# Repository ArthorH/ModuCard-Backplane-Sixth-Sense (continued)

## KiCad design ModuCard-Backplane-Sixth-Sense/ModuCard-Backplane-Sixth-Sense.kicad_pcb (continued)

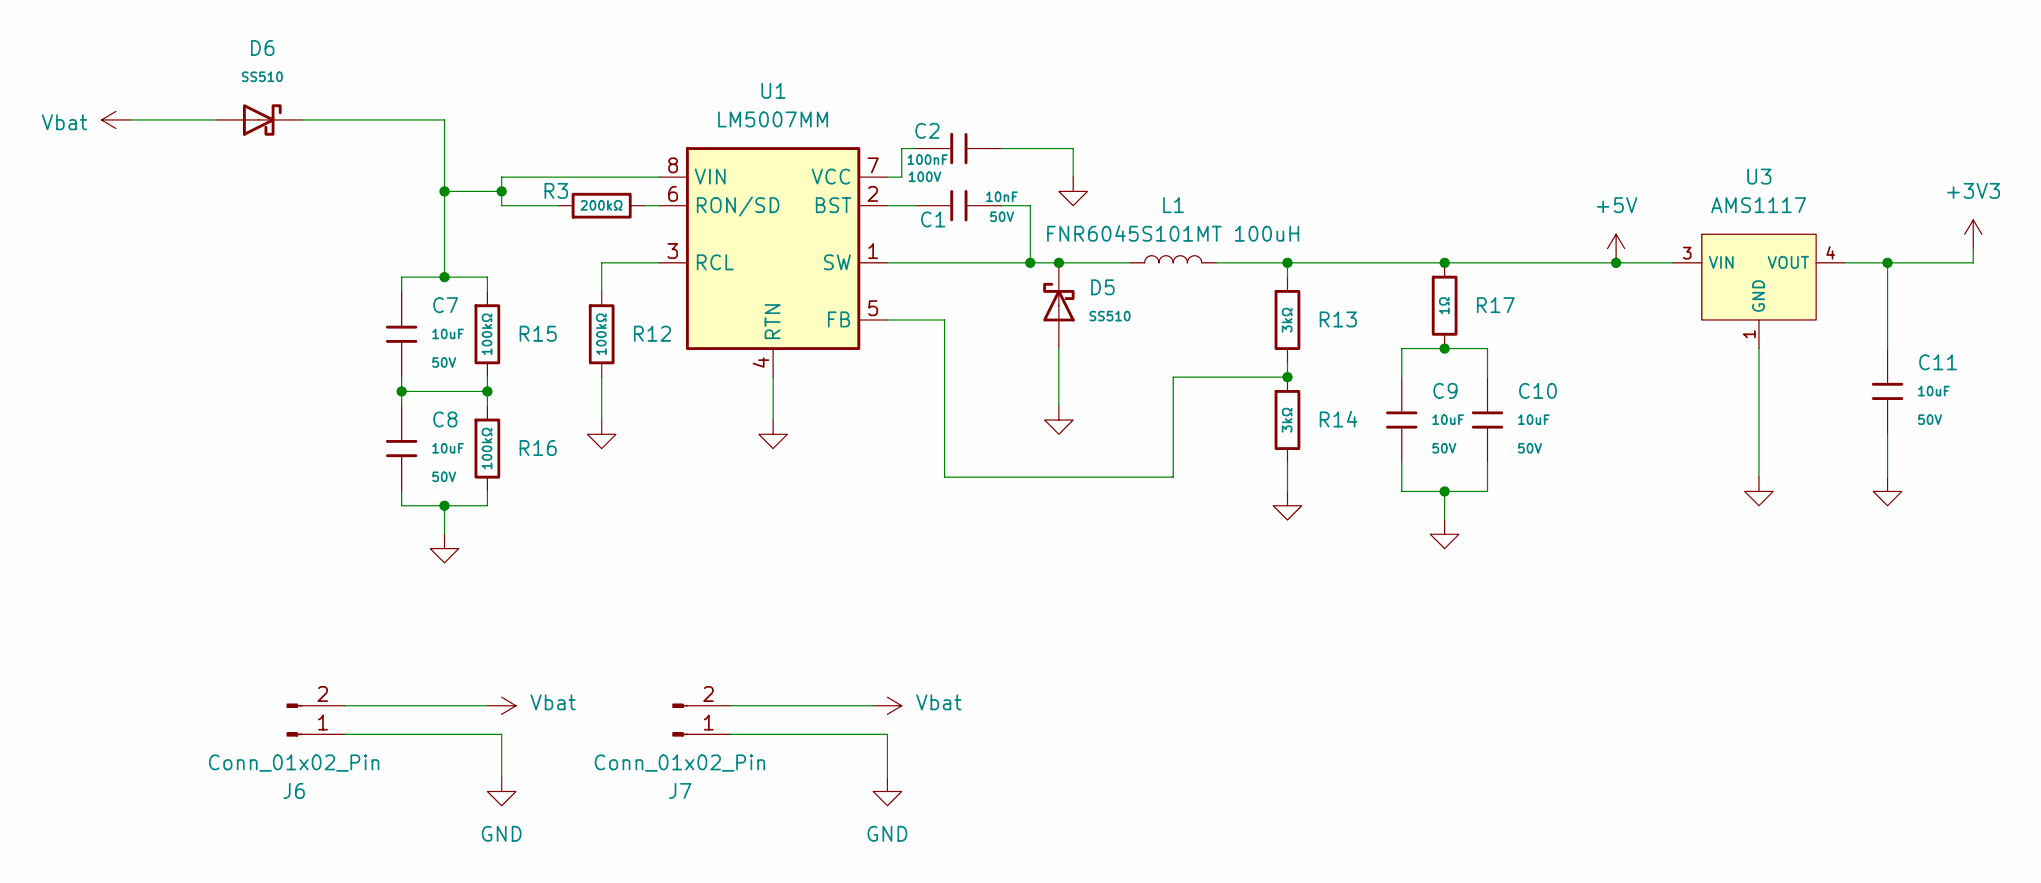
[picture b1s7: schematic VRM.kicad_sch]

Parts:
C1: 10nF; C_0805; Voltage Rated 50V; Tolerance ±10%; Part CL21B103KBANNNC; LCSC C1710
C2: 100nF; C_0805; Voltage Rated 100V; Tolerance ±10%; Part CL21B104KCFNNNE; LCSC C28233
C7, C8, C9, C10, C11: 10uF; C_0805; Voltage Rated 50V; Tolerance ±10%; Part GRM21BR61H106KE43L; LCSC C440198
D5, D6: SS510; D_SMA; Forward Voltage (Vf@If) 850mV@5A; Reverse Voltage (Vr) 100V; Part SS510; LCSC C18199171
J6, J7: Conn_01x02_Pin; AMASS_XT60-F_1x02_P7.20mm_Vertical
L1: FNR6045S101MT 100uH; L_Chilisin_BWVS00606020
R3: 200kΩ; R_0805; Overload Voltage (Max) 150V; Tolerance ±1%; Part 0805W8F2003T5E; LCSC C17539
R12, R15, R16: 100kΩ; R_0805; Overload Voltage (Max) 150V; Tolerance ±1%; Part 0805W8F1003T5E; LCSC C149504
R13, R14: 3kΩ; R_0603; Overload Voltage (Max) 75V; Tolerance ±1%; Part 0603WAF3001T5E; LCSC C4211
R17: 1Ω; R_0603; Overload Voltage (Max) 75V; Tolerance ±1%; Part 0603WAF100KT5E; LCSC C22936
U1: LM5007MM; MSOP-8_3x3mm_P0.65mm
U3: AMS1117; SOT-223-3_L6.5-W3.4-P2.30-LS7.0-BR; Output Voltage 3.3V; Dropout Voltage 1.3V@(800mA); Part AMS1117-3.3; LCSC C6186

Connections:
+3V3: C11.1, U3.2 (VOUT), U3.4 (VOUT); also elsewhere on the board
+5V: L1.2, R13.1, R17.1, U3.3 (VIN); also elsewhere on the board
GND: C2.2, C8.2, C9.2, C10.2, C11.2, D5.2, J6.1, J7.1, R12.2, R14.2, R16.2, U1.4 (RTN), U3.1 (GND); also elsewhere on the board
unnamed: C7.2, C8.1, R15.2, R16.1
unnamed: C9.1, C10.1, R17.2
unnamed: C1.1, U1.2 (BST)
unnamed: R13.2, R14.1, U1.5 (FB)
unnamed: R12.1, U1.3 (RCL)
unnamed: R3.2, U1.6 (RON/SD)
unnamed: C1.2, D5.1, L1.1, U1.1 (SW)
unnamed: C2.1, U1.7 (VCC)
unnamed: C7.1, D6.1, R3.1, R15.1, U1.8 (VIN)
Vbat: D6.2, J6.2, J7.2; also elsewhere on the board

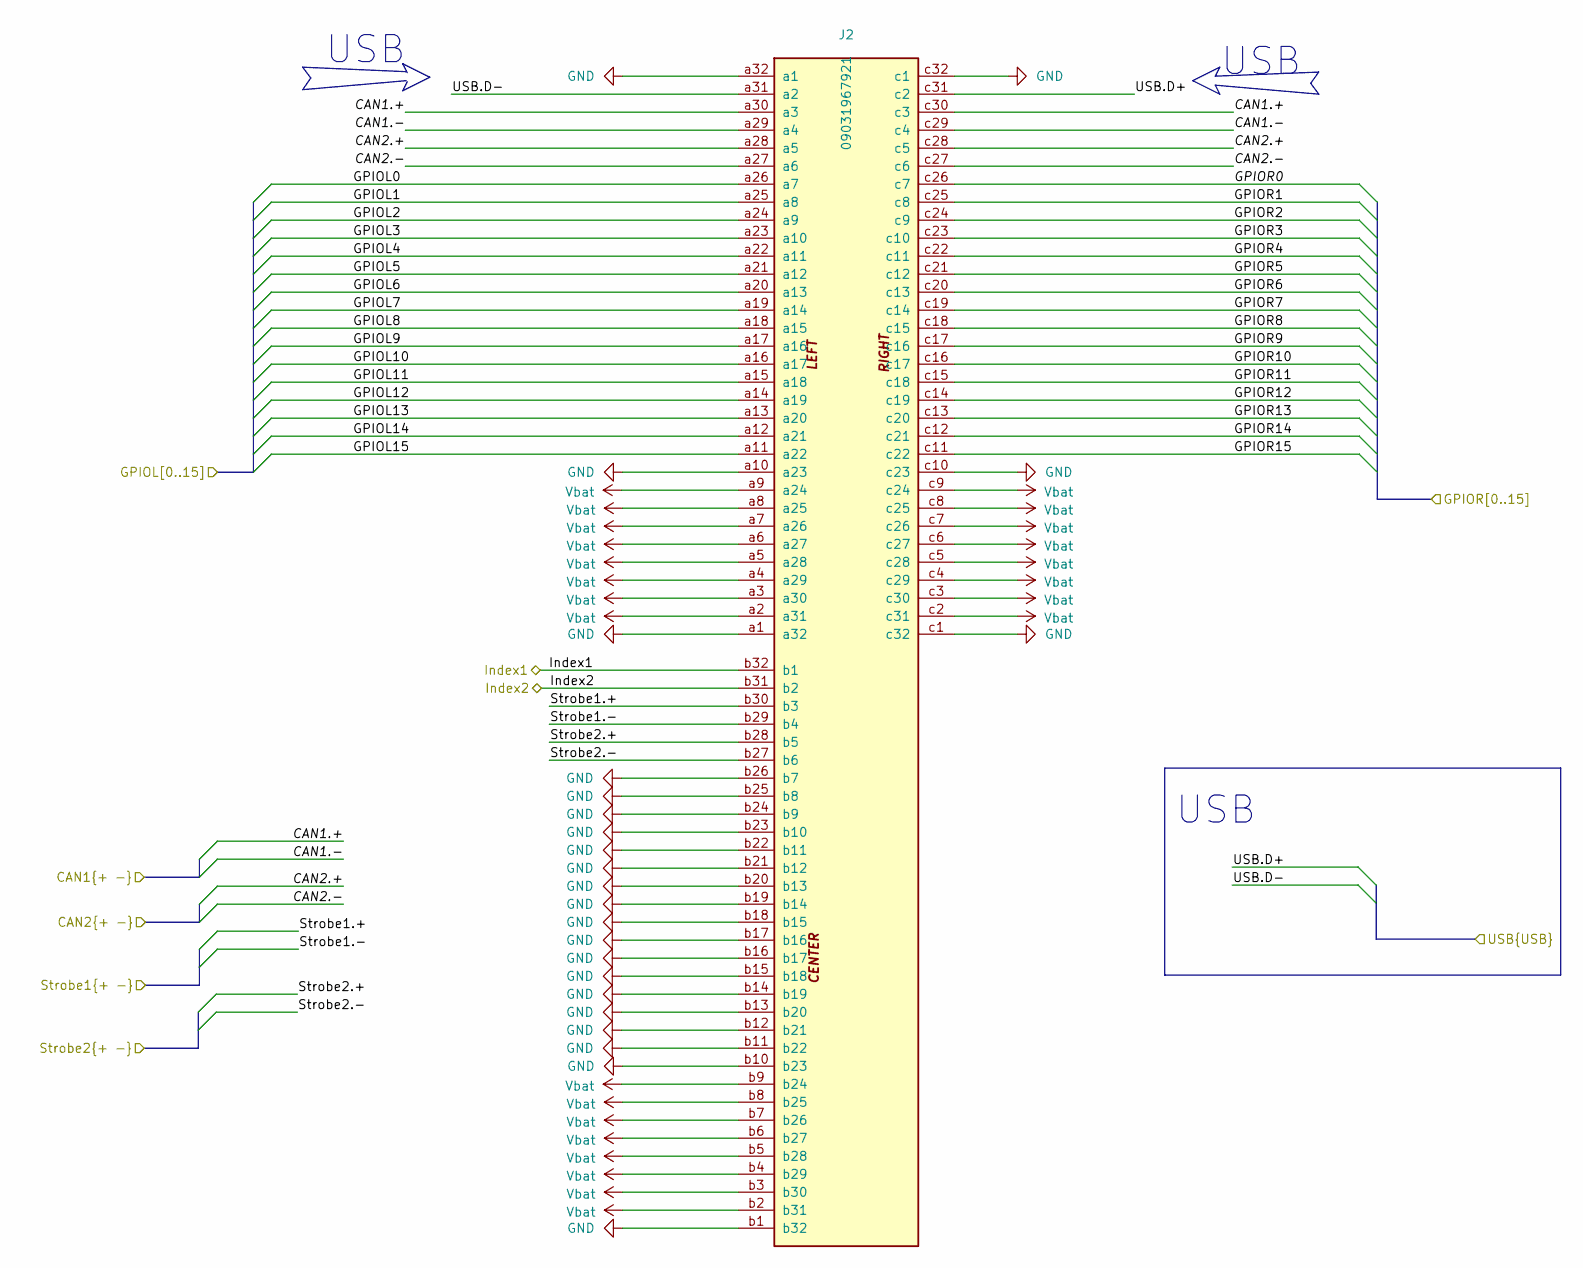
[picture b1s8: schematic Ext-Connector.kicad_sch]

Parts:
J2: 09031967921; DIN41612_R_3x32_Male_Horizontal_THT; PARTREV D

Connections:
/Can Split Terminators/CAN1.+: J2.a30 (a3), J2.c30 (c3); also elsewhere on the board
/Can Split Terminators/CAN1.-: J2.a29 (a4), J2.c29 (c4); also elsewhere on the board
/Can Split Terminators/CAN2.+: J2.a28 (a5), J2.c28 (c5); also elsewhere on the board
/Can Split Terminators/CAN2.-: J2.a27 (a6), J2.c27 (c6); also elsewhere on the board
/Can Split Terminators/Strobe1.+: J2.b30 (b3); also elsewhere on the board
/Can Split Terminators/Strobe1.-: J2.b29 (b4); also elsewhere on the board
/Ext-Connector/GPIOL0: J2.a26 (a7)
/Ext-Connector/GPIOL1: J2.a25 (a8)
/Ext-Connector/GPIOL2: J2.a24 (a9)
/Ext-Connector/GPIOL3: J2.a23 (a10)
/Ext-Connector/GPIOL4: J2.a22 (a11)
/Ext-Connector/GPIOL5: J2.a21 (a12)
/Ext-Connector/GPIOL6: J2.a20 (a13)
/Ext-Connector/GPIOL7: J2.a19 (a14)
/Ext-Connector/GPIOL8: J2.a18 (a15)
/Ext-Connector/GPIOL9: J2.a17 (a16)
/Ext-Connector/GPIOL10: J2.a16 (a17)
/Ext-Connector/GPIOL11: J2.a15 (a18)
/Ext-Connector/GPIOL12: J2.a14 (a19)
/Ext-Connector/GPIOL13: J2.a13 (a20)
/Ext-Connector/GPIOL14: J2.a12 (a21)
/Ext-Connector/GPIOL15: J2.a11 (a22)
/Ext-Connector/GPIOR0: J2.c26 (c7); also elsewhere on the board
/Ext-Connector/GPIOR1: J2.c25 (c8); also elsewhere on the board
/Ext-Connector/GPIOR2: J2.c24 (c9); also elsewhere on the board
/Ext-Connector/GPIOR3: J2.c23 (c10); also elsewhere on the board
/Ext-Connector/GPIOR4: J2.c22 (c11); also elsewhere on the board
/Ext-Connector/GPIOR5: J2.c21 (c12); also elsewhere on the board
/Ext-Connector/GPIOR6: J2.c20 (c13); also elsewhere on the board
/Ext-Connector/GPIOR7: J2.c19 (c14); also elsewhere on the board
/Ext-Connector/GPIOR8: J2.c18 (c15); also elsewhere on the board
/Ext-Connector/GPIOR9: J2.c17 (c16); also elsewhere on the board
/Ext-Connector/GPIOR10: J2.c16 (c17); also elsewhere on the board
/Ext-Connector/GPIOR11: J2.c15 (c18); also elsewhere on the board
/Ext-Connector/GPIOR12: J2.c14 (c19); also elsewhere on the board
/Ext-Connector/GPIOR13: J2.c13 (c20); also elsewhere on the board
/Ext-Connector/GPIOR14: J2.c12 (c21); also elsewhere on the board
/Ext-Connector/GPIOR15: J2.c11 (c22); also elsewhere on the board
/Ext-Connector/Index1: J2.b32 (b1); also elsewhere on the board
/Ext-Connector/Strobe2.+: J2.b28 (b5); also elsewhere on the board
/Ext-Connector/Strobe2.-: J2.b27 (b6); also elsewhere on the board
/Ext-Connector/USB.D+: J2.c31 (c2); also elsewhere on the board
/Ext-Connector/USB.D-: J2.a31 (a2); also elsewhere on the board
/Index2: J2.b31 (b2); also elsewhere on the board
GND: J2.a1 (a32), J2.a10 (a23), J2.a32 (a1), J2.b1 (b32), J2.b10 (b23), J2.b11 (b22), J2.b12 (b21), J2.b13 (b20), J2.b14 (b19), J2.b15 (b18), J2.b16 (b17), J2.b17 (b16), J2.b18 (b15), J2.b19 (b14), J2.b20 (b13), J2.b21 (b12), J2.b22 (b11), J2.b23 (b10), J2.b24 (b9), J2.b25 (b8), J2.b26 (b7), J2.c1 (c32), J2.c10 (c23), J2.c32 (c1); also elsewhere on the board
Vbat: J2.a2 (a31), J2.a3 (a30), J2.a4 (a29), J2.a5 (a28), J2.a6 (a27), J2.a7 (a26), J2.a8 (a25), J2.a9 (a24), J2.b2 (b31), J2.b3 (b30), J2.b4 (b29), J2.b5 (b28), J2.b6 (b27), J2.b7 (b26), J2.b8 (b25), J2.b9 (b24), J2.c2 (c31), J2.c3 (c30), J2.c4 (c29), J2.c5 (c28), J2.c6 (c27), J2.c7 (c26), J2.c8 (c25), J2.c9 (c24); also elsewhere on the board

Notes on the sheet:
USB

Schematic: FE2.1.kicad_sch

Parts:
C25, C26, C27, C29, C30, C31, C32, C33, C34, C36, C37, C38: 100nF; C_0402; Voltage Rated 50V; Tolerance ±10%; Part CL05B104KB54PNC; LCSC C307331
C35, C41: 10uF; C_0603; Voltage Rated 10V; Tolerance ±10%; Part CL10A106KP8NNNC; LCSC C19702
C39, C40: 12pF; C_0402; Voltage Rated 50V; Tolerance ±5%; Part 0402CG120J500NT; LCSC C1547
D9, D10: LED; LED_D3.0mm
D20, D22, D24, D26, D28, D30, D32: Green; D_0805; Part KT-0805G; LCSC C2297
D21, D23, D25, D27, D29, D31, D33: Yellow; D_0805; Part KT-0805Y; LCSC C2296
D34: Red; D_0603; Part KT-0603R; LCSC C2286
R2: 10kΩ; R_0402; Overload Voltage (Max) 50V; Tolerance ±1%; Part 0402WGF1002TCE; LCSC C25744
R27, R29: 100kΩ; R_0402; Overload Voltage (Max) 50V; Tolerance ±1%; Part 0402WGF1003TCE; LCSC C25741
R28: 47kΩ; R_0402; Overload Voltage (Max) 50V; Tolerance ±1%; Part 0402WGF4702TCE; LCSC C25792
R30: 2.7kΩ; R_0603; Overload Voltage (Max) 75V; Tolerance ±1%; Part 0603WAF2701T5E; LCSC C13167
R31, R32, R33, R34, R35, R36, R37, R38: 330Ω; R_0402; Overload Voltage (Max) 50V; Tolerance ±1%; Part 0402WGF3300TCE; LCSC C25104
U4: FE2.1; LQFP-48_7x7mm_P0.5mm; MPN FE2.1-CQFP48A; LCSC Part C39693
X2: X322512MSB4SI; CRYSTAL-SMD_4P-L3.2-W2.5-BL; Frequency Tolerance ±10ppm; Part X322512MSB4SI; LCSC C9002

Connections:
+5V: C27.1, C41.1, R28.1, U4.8 (VDD5); also elsewhere on the board
/Ext-Connector/USB.D+: U4.38 (DP7); also elsewhere on the board
/Ext-Connector/USB.D-: U4.37 (DM7); also elsewhere on the board
/FE2.1/DRV: D9.1 (K), D10.2 (A), D20.2, D21.1, D22.2, D23.1, D24.2, D25.1, D26.2, D27.1, D28.2, D29.1, D30.2, D31.1, D32.1, D33.2, R38.1, U4.1 (DRV)
/FE2.1/LED[1]: R31.1, U4.3 (LED[1])
/FE2.1/LED[2]: R32.1, U4.4 (LED[2])
/FE2.1/LED[3]: R33.1, U4.5 (LED[3])
/FE2.1/LED[4]: R34.1, U4.7 (LED[4])
/FE2.1/LED[5]: R35.1, U4.48 (LED[5])
/FE2.1/LED[6]: R36.1, U4.47 (LED[6])
/FE2.1/LED[7]: R37.1, U4.46 (LED[7])
/FE2.1/OVCJ1: R2.2, U4.45 (OVCJ1)
/FE2.1/OVCJ5: U4.43 (OVCJ5)
/FE2.1/PWRJ: U4.44 (PWRJ)
/FE2.1/TESTJ: U4.2 (TESTJ)
/FE2.1/USB1.D+: U4.19 (DP1); also elsewhere on the board
/FE2.1/USB1.D-: U4.18 (DM1); also elsewhere on the board
/FE2.1/USB2.D+: U4.17 (DP2); also elsewhere on the board
/FE2.1/USB2.D-: U4.16 (DM2); also elsewhere on the board
/FE2.1/USB3.D+: U4.14 (DP3); also elsewhere on the board
/FE2.1/USB3.D-: U4.13 (DM3); also elsewhere on the board
/FE2.1/USB4.D+: U4.12 (DP4); also elsewhere on the board
/FE2.1/USB4.D-: U4.11 (DM4); also elsewhere on the board
/FE2.1/USB5.D+: U4.33 (DP5); also elsewhere on the board
/FE2.1/USB5.D-: U4.32 (DM5); also elsewhere on the board
/FE2.1/USB6.D+: U4.35 (DP6); also elsewhere on the board
/FE2.1/USB6.D-: U4.34 (DM6); also elsewhere on the board
/FE2.1/USB_IN.D+: U4.30 (DPU); also elsewhere on the board
/FE2.1/USB_IN.D-: U4.29 (DMU); also elsewhere on the board
/FE2.1/VBUSM: R28.2, R29.1, U4.41 (VBUSM)
/FE2.1/VD18: C25.1, C30.1, C33.1, C35.1, U4.6 (VD18), U4.21 (VD_DLL), U4.25 (VDD18_O), U4.28 (VD18)
/FE2.1/VD33: C26.1, C29.1, C32.1, C34.1, C36.1, C37.1, C38.1, R2.1, R27.1, U4.9 (VD33_O), U4.15 (VD33), U4.20 (VD33), U4.26 (VD33), U4.31 (VD33), U4.36 (VD33), U4.42 (VD33)
/FE2.1/XIN: C39.1, U4.22 (XIN), X2.1 (OSC)
/FE2.1/XOUT: C40.1, U4.23 (XOUT), X2.3 (OSC)
/FE2.1/XRSTJ: C31.1, R27.2, U4.40 (XRSTJ)
GND: C25.2, C26.2, C27.2, C29.2, C30.2, C31.2, C32.2, C33.2, C34.2, C35.2, C36.2, C37.2, C38.2, C39.2, C40.2, C41.2, D34.1, R29.2, R30.2, U4.10 (VSS), U4.24 (VS_PLL), U4.39 (VSS), X2.2 (GND), X2.4 (GND); also elsewhere on the board
unnamed: D9.2 (A), D10.1 (K), D32.2, D33.1, R37.2
unnamed: D20.1, D21.2, R31.2
unnamed: D22.1, D23.2, R32.2
unnamed: D24.1, D25.2, R33.2
unnamed: D26.1, D27.2, R34.2
unnamed: D28.1, D29.2, R35.2
unnamed: D30.1, D31.2, R36.2
unnamed: D34.2, R38.2
unnamed: R30.1, U4.27 (REXT)

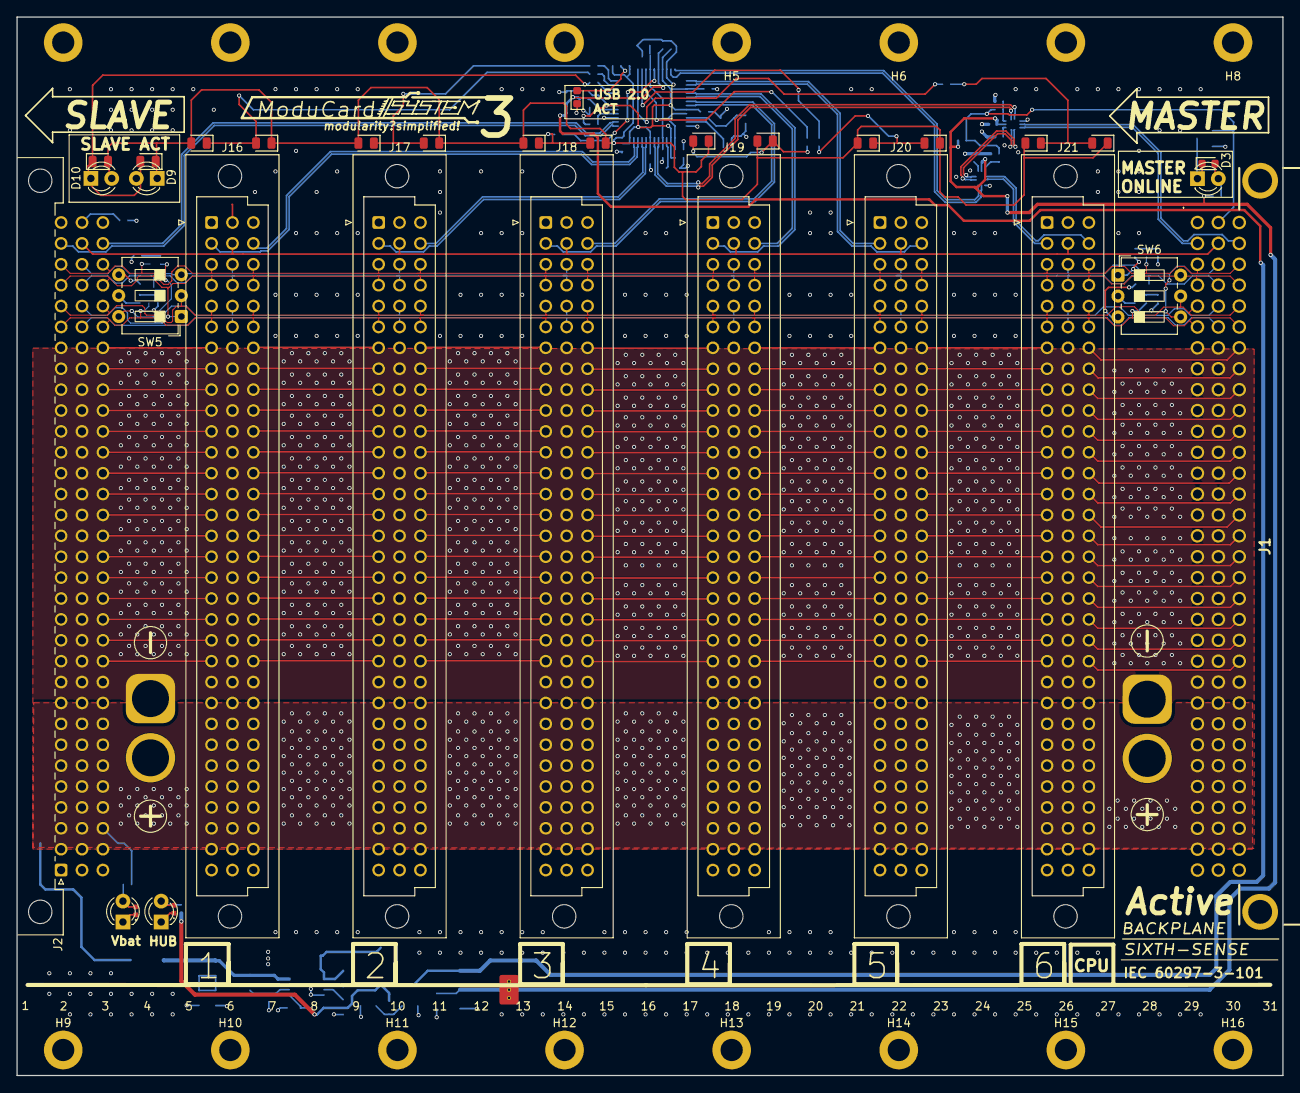
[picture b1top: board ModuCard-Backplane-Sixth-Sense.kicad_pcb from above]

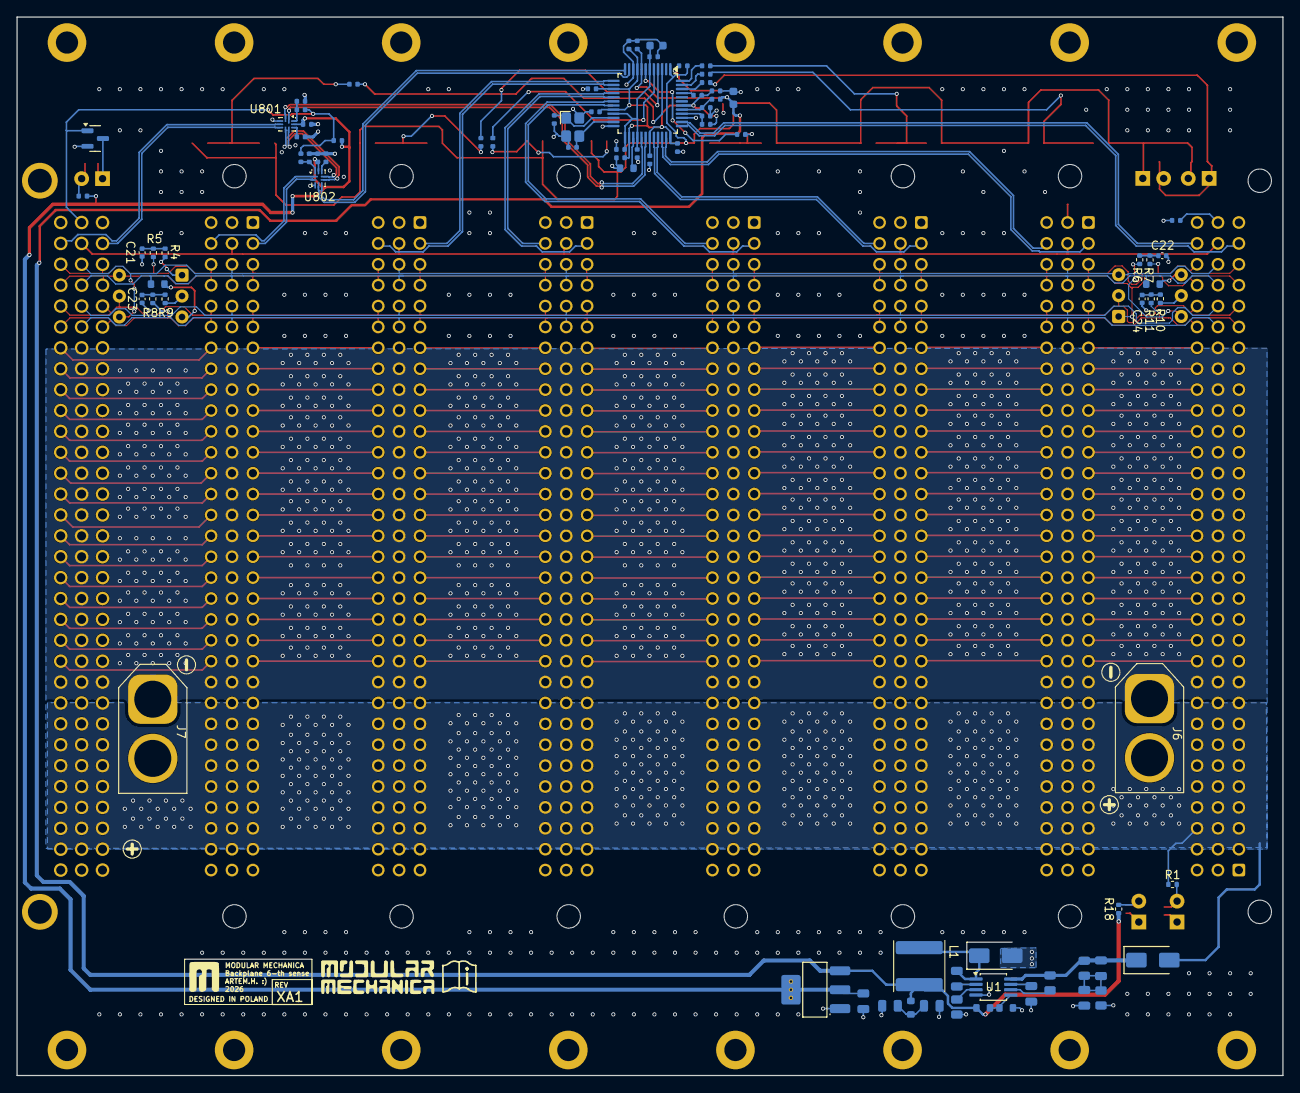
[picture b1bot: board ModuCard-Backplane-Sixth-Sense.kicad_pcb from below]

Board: 4 copper layers, 153.9 x 128.7 mm, 131 parts (82 on the bottom side), 200 nets.

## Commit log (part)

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2026-06-18 sch done
2026-06-27 erc -fix1
